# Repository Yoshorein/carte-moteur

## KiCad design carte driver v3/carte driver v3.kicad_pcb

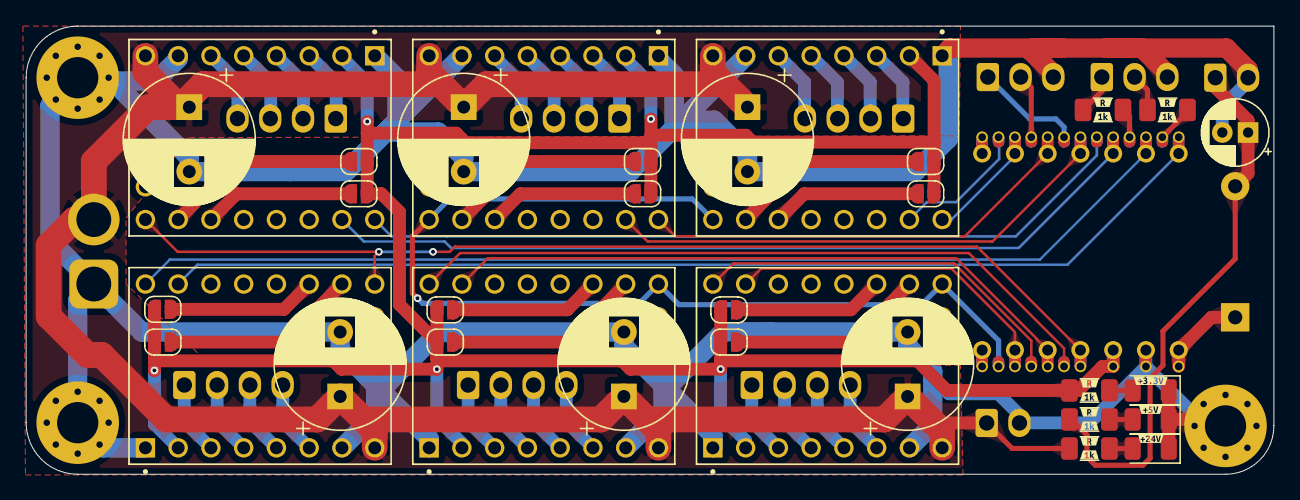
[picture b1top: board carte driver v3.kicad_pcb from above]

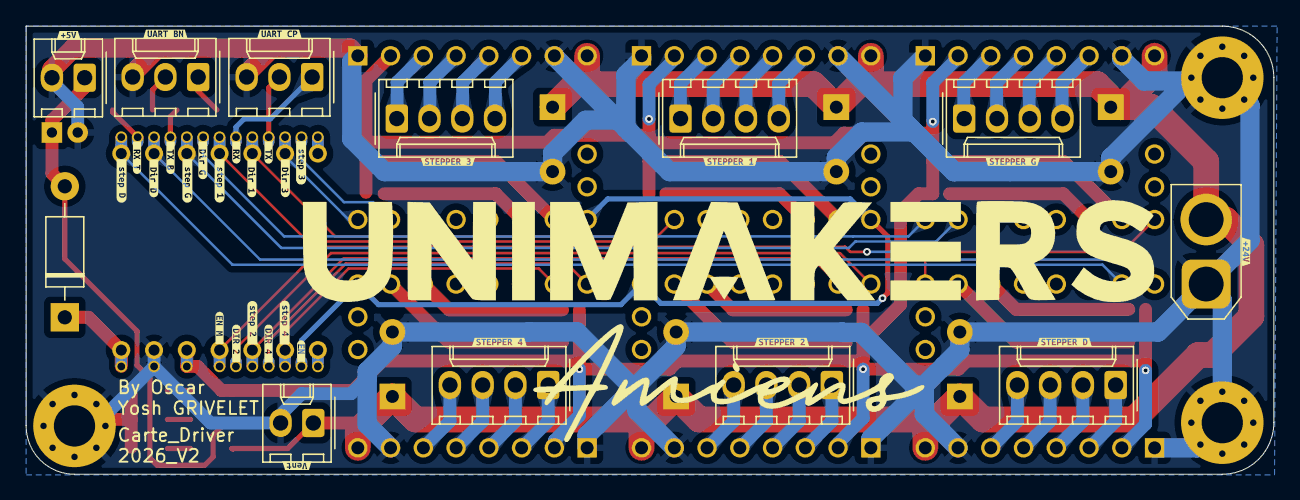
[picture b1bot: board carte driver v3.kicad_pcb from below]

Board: 2 copper layers, 96.8 x 34.8 mm, 91 parts (41 on the bottom side), 64 nets.

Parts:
C1, C2, C3, C4, C5, C6: 100µF; CP_Radial_D10.0mm_P5.00mm
C7: 100µF; CP_Radial_D5.0mm_P2.00mm
D1: D_Shottky; D_DO-41_SOD81_P10.16mm_Horizontal
D2, D3, D4: LED_Small; LED_1206_3216Metric
H1, H2, H3: MountingHole_Pad; MountingHole_3.2mm_M3_Pad_Via
J1: UART CP; Molex_KK-254_AE-6410-03A_1x03_P2.54mm_Vertical
J2: UART BONUS; Molex_KK-254_AE-6410-03A_1x03_P2.54mm_Vertical
J3: conn 24v; AMASS_XT30U-F_1x02_P5.0mm_Vertical
J4: conn 5v; Molex_KK-254_AE-6410-02A_1x02_P2.54mm_Vertical
J5: ventilo; Molex_KK-254_AE-6410-02A_1x02_P2.54mm_Vertical
J6: STEPPER G; Molex_KK-254_AE-6410-04A_1x04_P2.54mm_Vertical
J7: STEPPER 1; Molex_KK-254_AE-6410-04A_1x04_P2.54mm_Vertical
J8: STEPPER 3; Molex_KK-254_AE-6410-04A_1x04_P2.54mm_Vertical
J9: STEPPER D; Molex_KK-254_AE-6410-04A_1x04_P2.54mm_Vertical
J10: STEPPER 2; Molex_KK-254_AE-6410-04A_1x04_P2.54mm_Vertical
J11: STEPPER 4; Molex_KK-254_AE-6410-04A_1x04_P2.54mm_Vertical
JP11, JP12, JP21, JP22, JP31, JP32, JP41, JP42, JP51, JP52, JP61, JP62: Jumper_2_Open; SolderJumper-2_P1.3mm_Open_RoundedPad1.0x1.5mm
R1, R2, R3, R4, R5: 1k; R_1206_3216Metric_Pad1.30x1.75mm_HandSolder
U1, U2, U3, U4, U5, U6: TMC2209_SILENTSTEPSTICK; MODULE_TMC2209_SILENTSTEPSTICK
U10: XIAO-HALF-HOLE-23P; MOUDLE23P-SMD-2.54-21X17.8MM.kicad_mod.kicad_sym
kibuzzard-690E8D8B: G***; kibuzzard-690E8D8B
kibuzzard-690E8DC3: G***; kibuzzard-690E8DC3
kibuzzard-690E8DDF: G***; kibuzzard-690E8DDF
kibuzzard-690E8E20: G***; kibuzzard-690E8E20
kibuzzard-690E8E58: G***; kibuzzard-690E8E58
kibuzzard-690E8E91: G***; kibuzzard-690E8E91
kibuzzard-690E8EB4: G***; kibuzzard-690E8EB4
kibuzzard-690E8ECA: G***; kibuzzard-690E8ECA
kibuzzard-690E8EDD: G***; kibuzzard-690E8EDD
kibuzzard-690E8EED: G***; kibuzzard-690E8EED
kibuzzard-690E8EFE: G***; kibuzzard-690E8EFE
kibuzzard-690E8F3D: G***; kibuzzard-690E8F3D
kibuzzard-690E8F10: G***; kibuzzard-690E8F10
kibuzzard-690E8F27: G***; kibuzzard-690E8F27
kibuzzard-690E90CC: G***; kibuzzard-690E90CC
kibuzzard-690E90D9: G***; kibuzzard-690E90D9
kibuzzard-690E90FE: G***; kibuzzard-690E90FE
kibuzzard-690E92EA: G***; kibuzzard-690E92EA
kibuzzard-690E93A6: G***; kibuzzard-690E93A6
kibuzzard-690E93B3: G***; kibuzzard-690E93B3
kibuzzard-690E93BF: G***; kibuzzard-690E93BF
kibuzzard-690E924D: G***; kibuzzard-690E924D
kibuzzard-690E925F: G***; kibuzzard-690E925F
kibuzzard-690E929D: G***; kibuzzard-690E929D
kibuzzard-690E943A, kibuzzard-690E943A#2, kibuzzard-690E943A#3, kibuzzard-690E943A#4, kibuzzard-690E943A#5: G***; kibuzzard-690E943A
kibuzzard-690E9105: G***; kibuzzard-690E9105
kibuzzard-690E9271: G***; kibuzzard-690E9271
kibuzzard-690E9406, kibuzzard-690E9406#2, kibuzzard-690E9406#3, kibuzzard-690E9406#4, kibuzzard-690E9406#5: G***; kibuzzard-690E9406
kibuzzard-691087A0: G***; kibuzzard-691087A0
kibuzzard-691087AC: G***; kibuzzard-691087AC
kibuzzard-6910874F: G***; kibuzzard-6910874F
kibuzzard-6910875C: G***; kibuzzard-6910875C
kibuzzard-69108723: G***; kibuzzard-69108723
kibuzzard-69108793: G***; kibuzzard-69108793

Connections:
+3.3V: JP11.1 (A), JP12.1 (A), JP21.1 (A), JP22.1 (A), JP31.1 (A), JP32.1 (A), JP41.1 (A), JP42.1 (A), JP51.1 (A), JP52.1 (A), JP61.1 (A), JP62.1 (A), R3.1, U1.2 (VIO), U2.2 (VIO), U3.2 (VIO), U4.2 (VIO), U5.2 (VIO), U6.2 (VIO), U10.12 (VCC_3V3)
+5V: C7.1, D1.2 (A), J4.1, R5.1
+24V: C1.1, C2.1, C3.1, C4.1, C5.1, C6.1, J3.2, J5.1, R4.1, U1.8 (VM), U2.8 (VM), U3.8 (VM), U4.8 (VM), U5.8 (VM), U6.8 (VM)
DIR 1: U1.9 (DIR), U10.17 (GPIO40_CAM_SDA/I2S_WS)
DIR 2: U2.9 (DIR), U10.5 (GPIO5_D4/A4/I2C_SDA)
DIR 3: U3.9 (DIR), U10.6 (GPIO6_D5/A5/I2C_SCL)
DIR 4: U4.9 (DIR), U10.22 (GPIO12_DVP_Y7/SPI_MISO1)
DIR 5: U5.9 (DIR), U10.23 (GPIO13_DVP_PCLK/SPI_SCK1)
DIR 6: U6.9 (DIR), U10.2 (GPIO2_D1/A1)
EN: U2.16 (~EN), U3.16 (~EN), U4.16 (~EN), U5.16 (~EN), U10.21 (GPIO11_DVP_Y8/SPI_MOSI1)
EN M: U1.16 (~EN), U6.16 (~EN), U10.11 (GPIO9_D10/A10/MOSI)
GND: C1.2, C2.2, C3.2, C4.2, C5.2, C6.2, C7.2, D2.1 (K), D3.1 (K), D4.1 (K), H1.1, H2.1, H3.1, J1.3, J2.3, J3.1, J4.2, J5.2, U1.1 (GND), U1.7 (GND), U2.1 (GND), U2.7 (GND), U3.1 (GND), U3.7 (GND), U4.1 (GND), U4.7 (GND), U5.1 (GND), U5.7 (GND), U6.1 (GND), U6.7 (GND), U10.13 (GND)
unnamed: D1.1 (K), U10.14 (VBUS)
unnamed: D2.2 (A), R5.2
unnamed: D3.2 (A), R3.2
unnamed: D4.2 (A), R4.2
unnamed: J6.1, U1.3 (M1B)
unnamed: J6.2, U1.4 (M1A)
unnamed: J6.3, U1.5 (M2A)
unnamed: J6.4, U1.6 (M2B)
unnamed: J7.1, U2.3 (M1B)
unnamed: J7.2, U2.4 (M1A)
unnamed: J7.3, U2.5 (M2A)
unnamed: J7.4, U2.6 (M2B)
unnamed: J8.1, U3.3 (M1B)
unnamed: J8.2, U3.4 (M1A)
unnamed: J8.3, U3.5 (M2A)
unnamed: J8.4, U3.6 (M2B)
unnamed: J9.1, U4.3 (M1B)
unnamed: J9.2, U4.4 (M1A)
unnamed: J9.3, U4.5 (M2A)
unnamed: J9.4, U4.6 (M2B)
unnamed: J10.1, U5.3 (M1B)
unnamed: J10.2, U5.4 (M1A)
unnamed: J10.3, U5.5 (M2A)
unnamed: J10.4, U5.6 (M2B)
unnamed: J11.1, U6.3 (M1B)
unnamed: J11.2, U6.4 (M1A)
unnamed: J11.3, U6.5 (M2A)
unnamed: J11.4, U6.6 (M2B)
unnamed: JP11.2 (B), U1.15 (MS1)
unnamed: JP12.2 (B), U1.14 (MS2)
unnamed: JP21.2 (B), U2.15 (MS1)
unnamed: JP22.2 (B), U2.14 (MS2)
unnamed: JP31.2 (B), U3.15 (MS1)
unnamed: JP32.2 (B), U3.14 (MS2)
unnamed: JP41.2 (B), U4.15 (MS1)
unnamed: JP42.2 (B), U4.14 (MS2)
unnamed: JP51.2 (B), U5.15 (MS1)
unnamed: JP52.2 (B), U5.14 (MS2)
unnamed: JP61.2 (B), U6.15 (MS1)
unnamed: JP62.2 (B), U6.14 (MS2)
unnamed: R1.1, U10.15 (GPIO38_DVP_VSYNC/I2S_SD)
unnamed: R2.1, U10.16 (GPIO39_CAM_SCL/I2S_SCK)
RX: J1.1, U10.18 (GPIO41_PDM_DATA/RX1)
RX B: J2.1, R2.2
STEP 1: U1.10 (STEP), U10.3 (GPIO3_D2/A2)
STEP 2: U2.10 (STEP), U10.4 (GPIO4_D3/A3)
STEP 3: U3.10 (STEP), U10.20 (GPIO10_XMCLK/ADC_BAT)
STEP 4: U4.10 (STEP), U10.9 (GPIO7_D8/A8/SCK)
STEP 5: U5.10 (STEP), U10.10 (GPIO8_D9/A9/MISO)
STEP 6: U6.10 (STEP), U10.1 (GPIO1_D0/A0)
TX: J1.2, U10.19 (GPIO42_PDM_CLK/TX1)
TX B: J2.2, R1.2

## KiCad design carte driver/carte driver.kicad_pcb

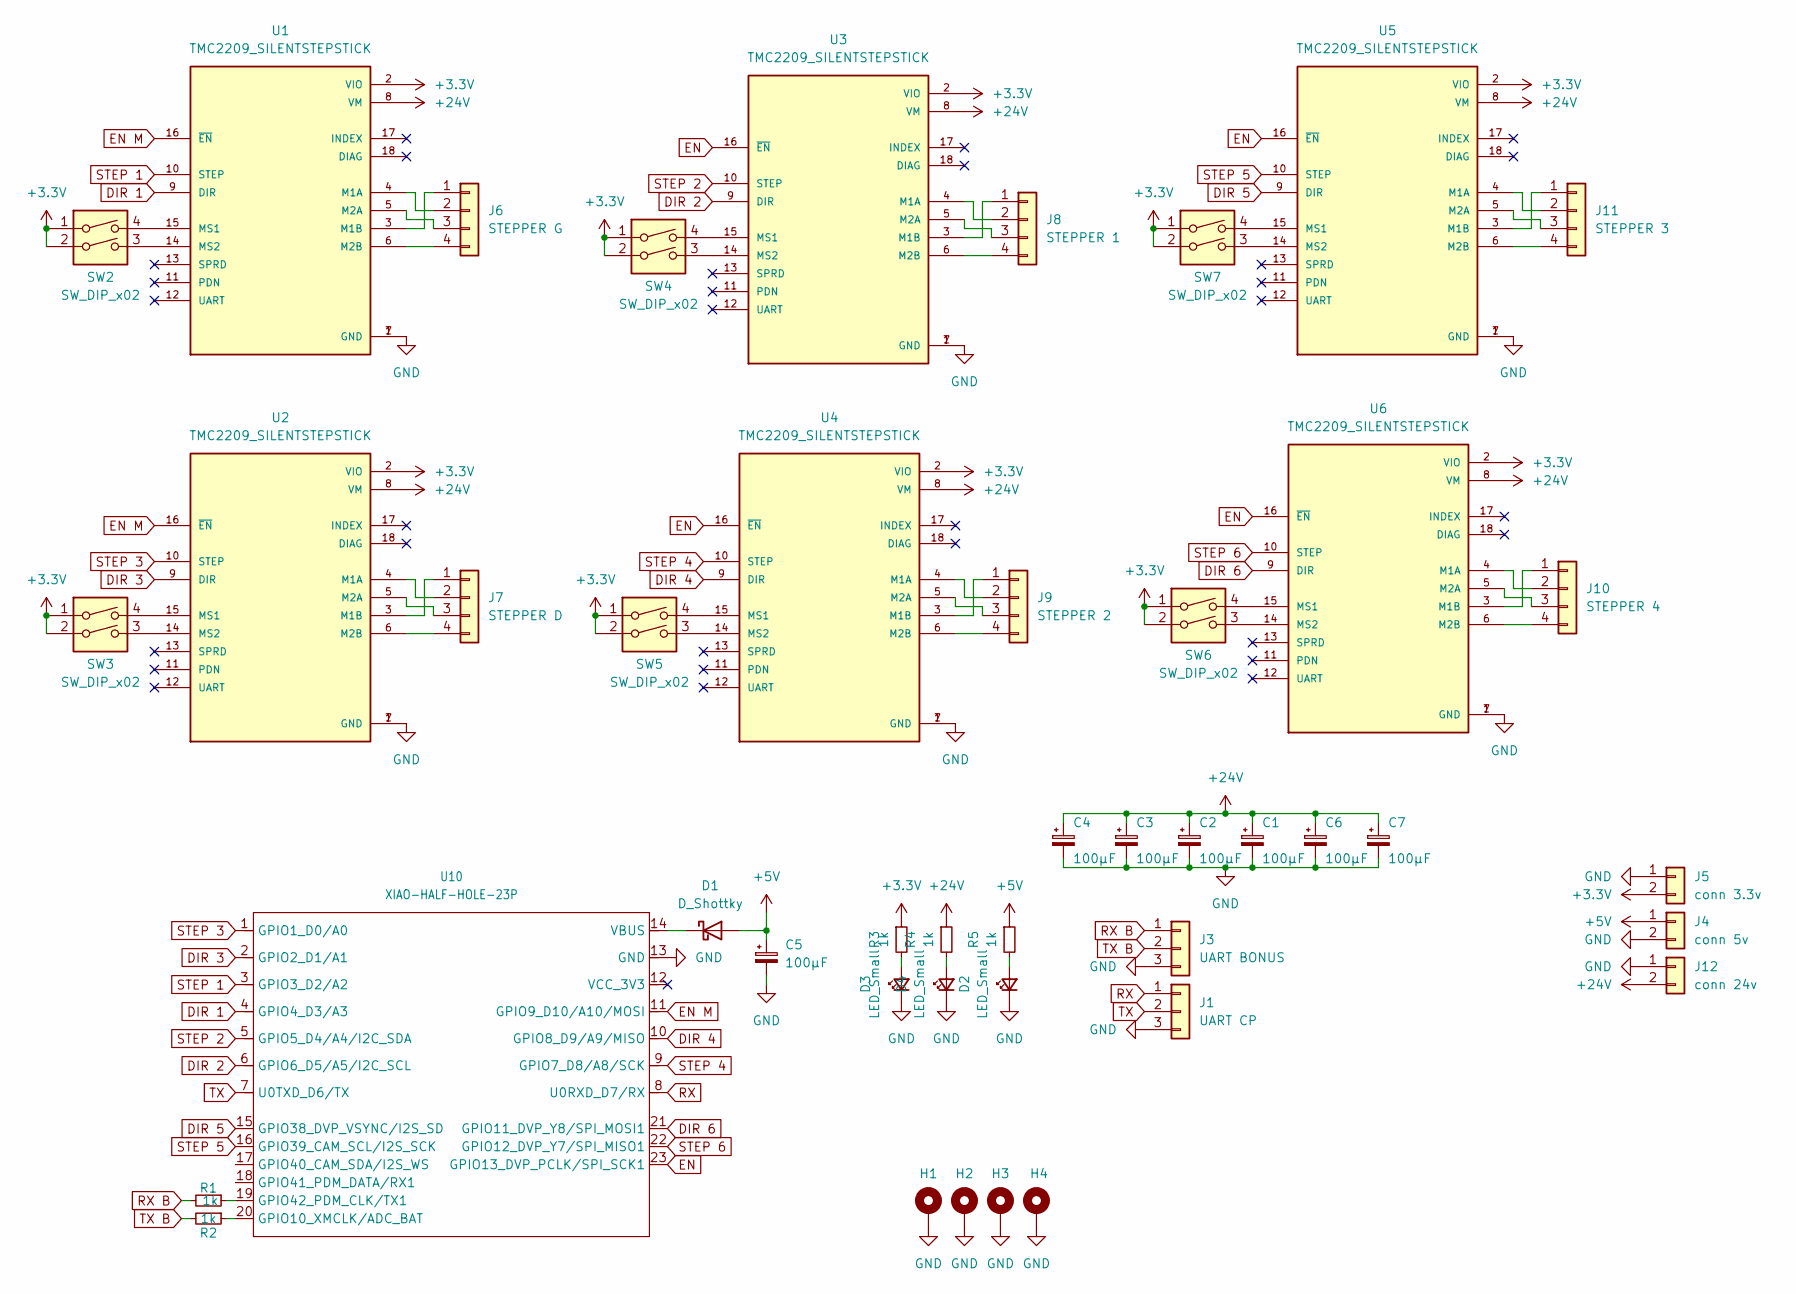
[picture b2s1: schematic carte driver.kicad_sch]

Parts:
C1, C2, C3, C4, C5, C6, C7: 100µF; CP_Radial_D10.0mm_P5.00mm
D1: D_Shottky; D_DO-41_SOD81_P10.16mm_Horizontal
D2, D3, D4: LED_Small; LED_1206_3216Metric
H1, H2, H3, H4: MountingHole_Pad; MountingHole_3.2mm_M3_Pad_Via
J1: UART CP; Molex_KK-254_AE-6410-03A_1x03_P2.54mm_Vertical
J3: UART BONUS; Molex_KK-254_AE-6410-03A_1x03_P2.54mm_Vertical
J4: conn 5v; Molex_KK-254_AE-6410-02A_1x02_P2.54mm_Vertical
J5: conn 3.3v; AMASS_XT30U-F_1x02_P5.0mm_Vertical
J6: STEPPER G; Molex_KK-254_AE-6410-04A_1x04_P2.54mm_Vertical
J7: STEPPER D; Molex_KK-254_AE-6410-04A_1x04_P2.54mm_Vertical
J8: STEPPER 1; Molex_KK-254_AE-6410-04A_1x04_P2.54mm_Vertical
J9: STEPPER 2; Molex_KK-254_AE-6410-04A_1x04_P2.54mm_Vertical
J10: STEPPER 4; Molex_KK-254_AE-6410-04A_1x04_P2.54mm_Vertical
J11: STEPPER 3; Molex_KK-254_AE-6410-04A_1x04_P2.54mm_Vertical
J12: conn 24v; AMASS_XT60-F_1x02_P7.20mm_Vertical
R1, R2, R3, R4, R5: 1k; R_1206_3216Metric_Pad1.30x1.75mm_HandSolder
SW2, SW3, SW4, SW5, SW6, SW7: SW_DIP_x02; SW_DIP_SPSTx02_Slide_9.78x7.26mm_W7.62mm_P2.54mm
U1, U2, U3, U4, U5, U6: TMC2209_SILENTSTEPSTICK; MODULE_TMC2209_SILENTSTEPSTICK; PARTREV 1.20
U10: XIAO-HALF-HOLE-23P; MOUDLE23P-SMD-2.54-21X17.8MM.kicad_mod.kicad_sym

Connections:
+3.3V: J5.2, R3.1, SW2.1, SW2.2, SW3.1, SW3.2, SW4.1, SW4.2, SW5.1, SW5.2, SW6.1, SW6.2, SW7.1, SW7.2, U1.2 (VIO), U2.2 (VIO), U3.2 (VIO), U4.2 (VIO), U5.2 (VIO), U6.2 (VIO)
+5V: C5.1, D1.2 (A), J4.1, R5.1
+24V: C1.1, C2.1, C3.1, C4.1, C6.1, C7.1, J12.2, R4.1, U1.8 (VM), U2.8 (VM), U3.8 (VM), U4.8 (VM), U5.8 (VM), U6.8 (VM)
DIR 1: U1.9 (DIR), U10.4 (GPIO4_D3/A3)
DIR 2: U3.9 (DIR), U10.6 (GPIO6_D5/A5/I2C_SCL)
DIR 3: U2.9 (DIR), U10.2 (GPIO2_D1/A1)
DIR 4: U4.9 (DIR), U10.10 (GPIO8_D9/A9/MISO)
DIR 5: U5.9 (DIR), U10.15 (GPIO38_DVP_VSYNC/I2S_SD)
DIR 6: U6.9 (DIR), U10.21 (GPIO11_DVP_Y8/SPI_MOSI1)
EN: U3.16 (~EN), U4.16 (~EN), U5.16 (~EN), U6.16 (~EN), U10.23 (GPIO13_DVP_PCLK/SPI_SCK1)
EN M: U1.16 (~EN), U2.16 (~EN), U10.11 (GPIO9_D10/A10/MOSI)
GND: C1.2, C2.2, C3.2, C4.2, C5.2, C6.2, C7.2, D2.1 (K), D3.1 (K), D4.1 (K), H1.1, H2.1, H3.1, H4.1, J1.3, J3.3, J4.2, J5.1, J12.1, U1.1 (GND), U1.7 (GND), U2.1 (GND), U2.7 (GND), U3.1 (GND), U3.7 (GND), U4.1 (GND), U4.7 (GND), U5.1 (GND), U5.7 (GND), U6.1 (GND), U6.7 (GND), U10.13 (GND)
unnamed: D1.1 (K), U10.14 (VBUS)
unnamed: D2.2 (A), R5.2
unnamed: D3.2 (A), R3.2
unnamed: D4.2 (A), R4.2
unnamed: J6.1, U1.3 (M1B)
unnamed: J6.2, U1.4 (M1A)
unnamed: J6.3, U1.5 (M2A)
unnamed: J6.4, U1.6 (M2B)
unnamed: J7.1, U2.3 (M1B)
unnamed: J7.2, U2.4 (M1A)
unnamed: J7.3, U2.5 (M2A)
unnamed: J7.4, U2.6 (M2B)
unnamed: J8.1, U3.3 (M1B)
unnamed: J8.2, U3.4 (M1A)
unnamed: J8.3, U3.5 (M2A)
unnamed: J8.4, U3.6 (M2B)
unnamed: J9.1, U4.3 (M1B)
unnamed: J9.2, U4.4 (M1A)
unnamed: J9.3, U4.5 (M2A)
unnamed: J9.4, U4.6 (M2B)
unnamed: J10.1, U6.3 (M1B)
unnamed: J10.2, U6.4 (M1A)
unnamed: J10.3, U6.5 (M2A)
unnamed: J10.4, U6.6 (M2B)
unnamed: J11.1, U5.3 (M1B)
unnamed: J11.2, U5.4 (M1A)
unnamed: J11.3, U5.5 (M2A)
unnamed: J11.4, U5.6 (M2B)
unnamed: SW2.4, U1.15 (MS1)
unnamed: SW2.3, U1.14 (MS2)
unnamed: SW3.4, U2.15 (MS1)
unnamed: SW3.3, U2.14 (MS2)
unnamed: SW4.4, U3.15 (MS1)
unnamed: SW4.3, U3.14 (MS2)
unnamed: SW5.4, U4.15 (MS1)
unnamed: SW5.3, U4.14 (MS2)
unnamed: SW7.4, U5.15 (MS1)
unnamed: SW7.3, U5.14 (MS2)
unnamed: SW6.4, U6.15 (MS1)
unnamed: SW6.3, U6.14 (MS2)
unnamed: R2.1, U10.20 (GPIO10_XMCLK/ADC_BAT)
unnamed: R1.1, U10.19 (GPIO42_PDM_CLK/TX1)
RX: J1.1, U10.8 (U0RXD_D7/RX)
RX B: J3.1, R1.2
STEP 1: U1.10 (STEP), U10.3 (GPIO3_D2/A2)
STEP 2: U3.10 (STEP), U10.5 (GPIO5_D4/A4/I2C_SDA)
STEP 3: U2.10 (STEP), U10.1 (GPIO1_D0/A0)
STEP 4: U4.10 (STEP), U10.9 (GPIO7_D8/A8/SCK)
STEP 5: U5.10 (STEP), U10.16 (GPIO39_CAM_SCL/I2S_SCK)
STEP 6: U6.10 (STEP), U10.22 (GPIO12_DVP_Y7/SPI_MISO1)
TX: J1.2, U10.7 (U0TXD_D6/TX)
TX B: J3.2, R2.2

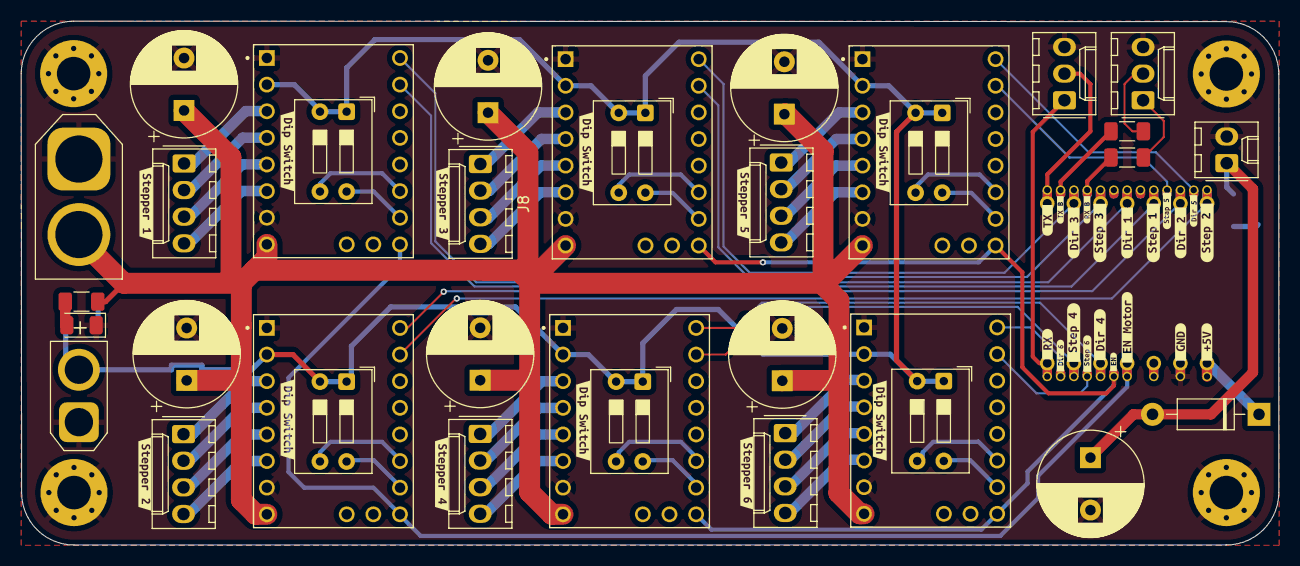
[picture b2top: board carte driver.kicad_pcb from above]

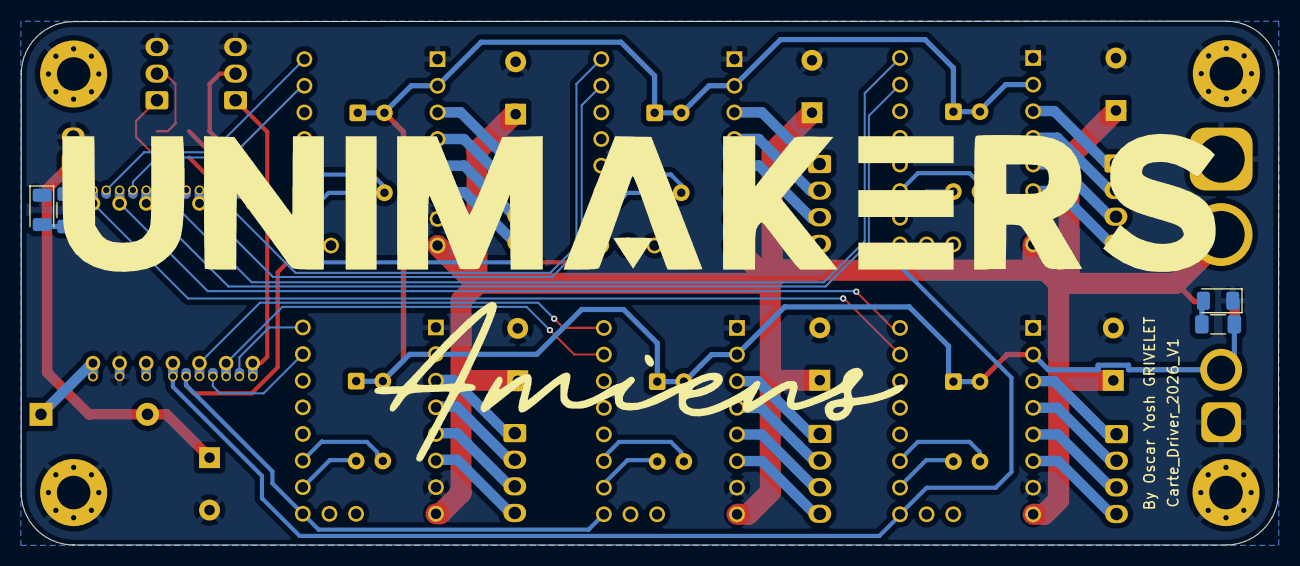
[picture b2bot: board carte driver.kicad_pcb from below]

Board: 2 copper layers, 120.0 x 50.0 mm, 76 parts (4 on the bottom side), 64 nets.

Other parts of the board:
kibuzzard-67ED8648: G***; kibuzzard-67ED8648
kibuzzard-67EE6BB1, kibuzzard-67EE6BB1#2, kibuzzard-67EE6BB1#3, kibuzzard-67EE6BB1#4, kibuzzard-67EE6BB1#5, kibuzzard-67EE6BB1#6: G***; kibuzzard-67EE6BB1
kibuzzard-68F7E1A4: G***; kibuzzard-68F7E1A4
kibuzzard-68F7E4A0: G***; kibuzzard-68F7E4A0
kibuzzard-68F7E5B2: G***; kibuzzard-68F7E5B2
kibuzzard-68F7E5C0: G***; kibuzzard-68F7E5C0
kibuzzard-68F7E5C7: G***; kibuzzard-68F7E5C7
kibuzzard-68F7E5D0: G***; kibuzzard-68F7E5D0
kibuzzard-68F7E5E0: G***; kibuzzard-68F7E5E0
kibuzzard-68F7E5E6: G***; kibuzzard-68F7E5E6
kibuzzard-68F7E5EE: G***; kibuzzard-68F7E5EE
kibuzzard-68F7E6E6: G***; kibuzzard-68F7E6E6
kibuzzard-68F7E6FB: G***; kibuzzard-68F7E6FB
kibuzzard-68F7E48E: G***; kibuzzard-68F7E48E
kibuzzard-68F7E49A: G***; kibuzzard-68F7E49A
kibuzzard-68F7E57E: G***; kibuzzard-68F7E57E
kibuzzard-68F7E70E: G***; kibuzzard-68F7E70E
kibuzzard-68F7E71B: G***; kibuzzard-68F7E71B
kibuzzard-68F7E74E: G***; kibuzzard-68F7E74E
kibuzzard-68F7E205: G***; kibuzzard-68F7E205
kibuzzard-68F7E494: G***; kibuzzard-68F7E494
kibuzzard-68F7E766: G***; kibuzzard-68F7E766
kibuzzard-68F7E774: G***; kibuzzard-68F7E774
kibuzzard-68F7E782: G***; kibuzzard-68F7E782
kibuzzard-68F7E793: G***; kibuzzard-68F7E793
kibuzzard-690B42CF: G***; kibuzzard-690B42CF
kibuzzard-690B42EC: G***; kibuzzard-690B42EC

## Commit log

2025-10-20 c'est l'heure de dodo j'ai bien taffé
2025-10-21 pret pour check
2025-10-21 debut etiquettes
2025-10-22 suite etiquettes
2025-11-03 apdavph
2025-11-03 caph
2025-11-04 some fixes
2025-11-04 ajout logo
2025-11-05 drawing
2025-11-05 changes power input and draw modif
2025-11-05 boh il y a des trucs à changé ducoup
2025-11-06 deso alph
2025-11-07 V3 start
2025-11-07 v3 fin routage
    on espere que c'est le cas
2025-11-09 Fin v3 avec annotation
    ça peut partir en prod
2025-11-12 allez
2025-11-12 pareil
2025-11-15 fixes
